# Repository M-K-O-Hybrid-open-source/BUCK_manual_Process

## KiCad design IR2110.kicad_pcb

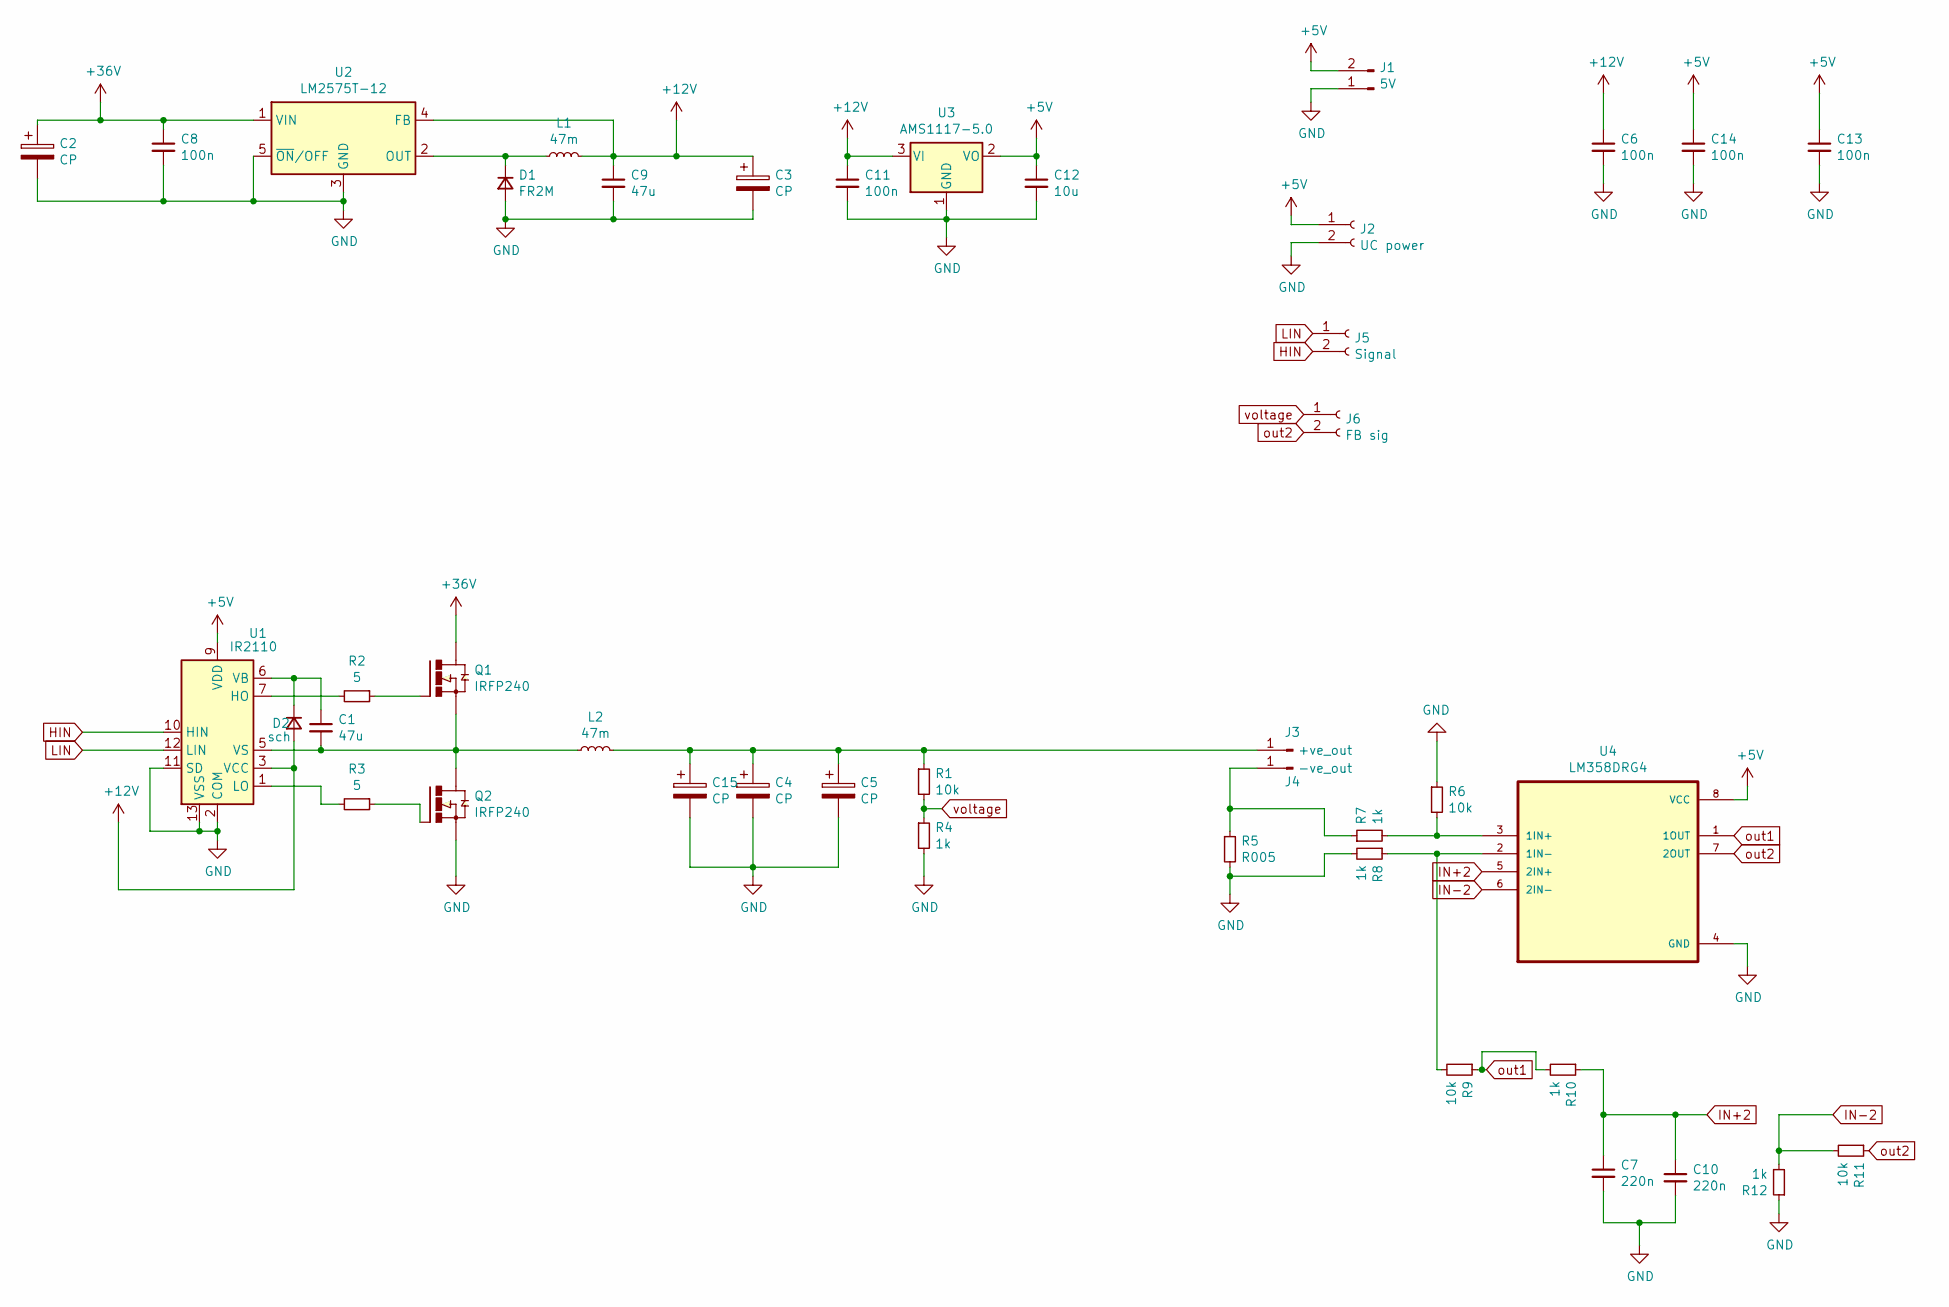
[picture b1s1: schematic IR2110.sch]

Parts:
C1, C9: 47u; C_0805_2012Metric
C2, C3, C4, C5, C15: CP; CP_Radial_D8.0mm_P5.00mm
C6, C8, C11, C13, C14: 100n; C_0805_2012Metric
C7, C10: 220n; C_0805_2012Metric
C12: 10u; C_0805_2012Metric
D1: FR2M; D_SMB
D2: sch; D_SMB
J1: 5V; PinSocket_1x02_P2.54mm_Vertical
J2: UC power; PinHeader_1x02_P2.54mm_Horizontal
J3: +ve_out; SolderWirePad_1x01_SMD_1x2mm
J4: -ve_out; SolderWirePad_1x01_SMD_1x2mm
J5: Signal; PinHeader_1x02_P2.54mm_Horizontal
J6: FB sig; PinHeader_1x02_P2.54mm_Horizontal
L1: 47m; L_Toroid_Horizontal_D3.2mm_P6.40mm_Diameter3-5mm_Amidon-T12
L2: 47m; L_Toroid_Vertical_L25.4mm_W14.7mm_P12.20mm_Vishay_TJ5
Q1, Q2: IRFP240; TO-247-3_Vertical; PARTREV B
R1, R6, R9, R11: 10k; R_0805_2012Metric
R2, R3: 5; R_Axial_DIN0204_L3.6mm_D1.6mm_P1.90mm_Vertical
R4, R7, R8, R10, R12: 1k; R_0805_2012Metric
R5: R005; R_2512_6332Metric
U1: IR2110; DIP-14_W7.62mm
U2: LM2575T-12; TO-220F-5_P3.4x3.7mm_StaggerEven_Lead3.5mm_Vertical
U3: AMS1117-5.0; SOT-223-3_TabPin2
U4: LM358DRG4; SOIC127P599X175-8N

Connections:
+5V: C12.1, C13.1, C14.1, J1.2, J2.1, U1.9 (VDD), U3.2 (VO), U4.8 (VCC)
+12V: C3.1, C6.1, C9.1, C11.1, D2.2 (A), L1.2, U1.3 (VCC), U2.4 (FB), U3.3 (VI)
+36V: C2.1, C8.1, Q1.2, U2.1 (VIN)
GND: C2.2, C3.2, C4.2, C5.2, C6.2, C7.2, C8.2, C9.2, C10.2, C11.2, C12.2, C13.2, C14.2, C15.2, D1.2 (A), J1.1, J2.2, Q2.3, R4.2, R5.2, R6.1, R8.2, R12.1, U1.2 (COM), U1.11 (SD), U1.13 (VSS), U2.3 (GND), U2.5 (~ON~/OFF), U3.1 (GND), U4.4 (GND)
HIN: J5.2, U1.10 (HIN)
IN+2: C7.1, C10.1, R10.1, U4.5 (2IN+)
IN-2: R11.2, R12.2, U4.6 (2IN-)
LIN: J5.1, U1.12 (LIN)
unnamed: C1.1, D2.1 (K), U1.6 (VB)
unnamed: C1.2, L2.1, Q1.3, Q2.2, U1.5 (VS)
unnamed: C4.1, C5.1, C15.1, J3.1, L2.2, R1.1
unnamed: D1.1 (K), L1.1, U2.2 (OUT)
unnamed: J4.1, R5.1, R7.1
unnamed: Q1.1, R2.1
unnamed: Q2.1, R3.1
unnamed: R2.2, U1.7 (HO)
unnamed: R3.2, U1.1 (LO)
unnamed: R6.2, R7.2, U4.3 (1IN+)
unnamed: R8.1, R9.2, U4.2 (1IN-)
out1: R9.1, R10.2, U4.1 (1OUT)
out2: J6.2, R11.1, U4.7 (2OUT)
voltage: J6.1, R1.2, R4.1

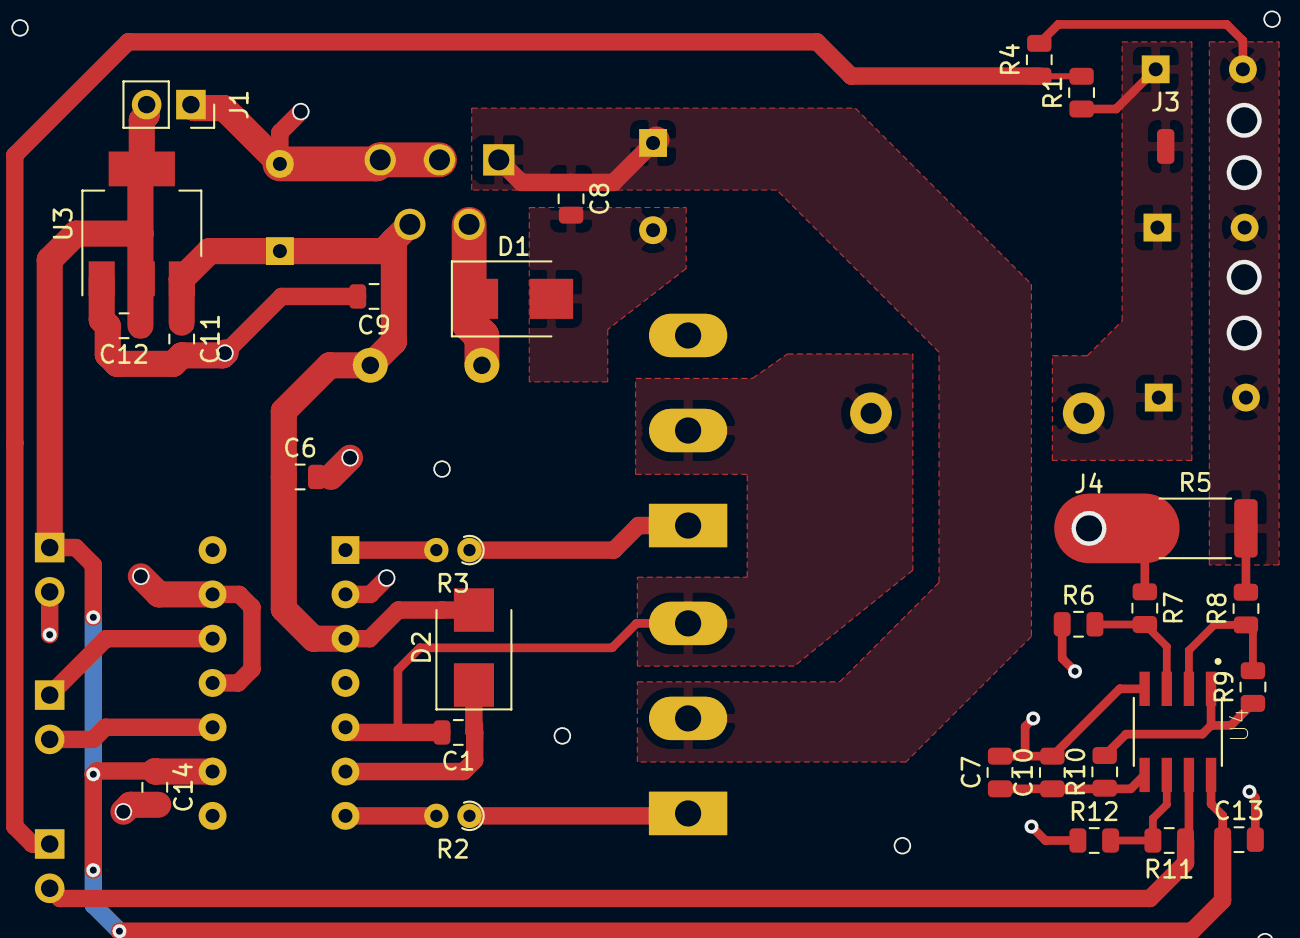
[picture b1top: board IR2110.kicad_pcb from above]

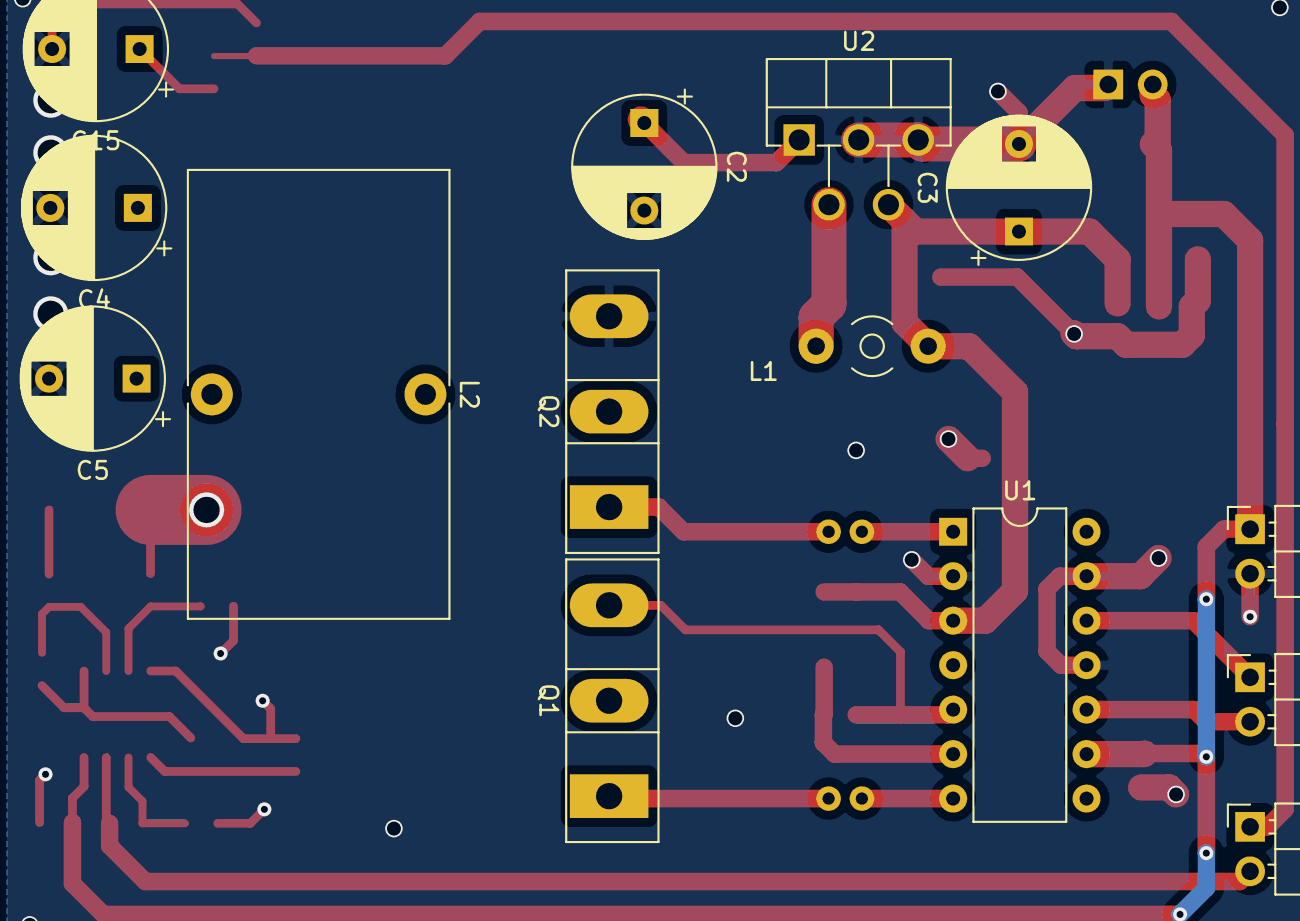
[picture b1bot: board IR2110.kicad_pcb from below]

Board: 2 copper layers, 43 parts (14 on the bottom side), 22 nets.
